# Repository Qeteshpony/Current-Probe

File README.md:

# Current-Probe

[Hardware Documentation](https://qeteshpony.github.io/Current-Probe)

A simple board to turn any oscilloscope into a current meter by running the load through the 4mm Terminals and connecting your oscilloscope to the BNC terminal. 

The resistor footprint takes a 2512 SMD resistor which usually come with a rating of 1 to 3, sometimes 5 watts which is enough to run several amps through this board. 

The connector footprints are made for the `Altech/Hirschmann PB 4` 4mm test jacks that take a standard 4mm test lead. 

The BNC connector footprint is for the `Amphenol B6252HB` but there's lots of cheap, compatible connectors with the same footprint available

You can also use the M3 screw holes to connect to this board since they are wired in parallel to the connectors closest to each.

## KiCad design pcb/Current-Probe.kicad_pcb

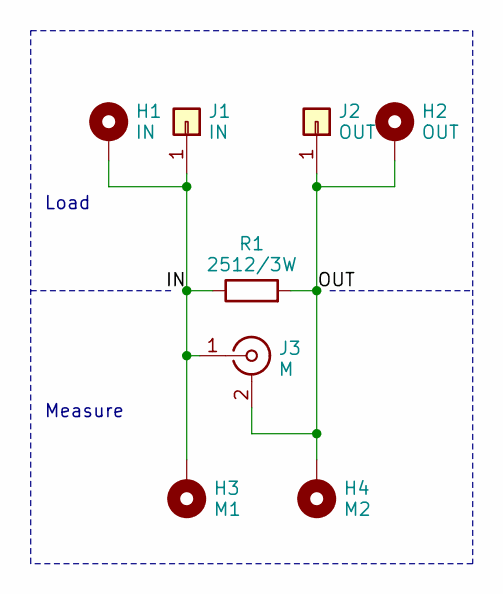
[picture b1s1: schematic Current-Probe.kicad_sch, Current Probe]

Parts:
H1: IN; MountingHole_3.2mm_M3_Pad_Via
H2: OUT; MountingHole_3.2mm_M3_Pad_Via
H3: M1; MountingHole_3.2mm_M3_Pad_Via
H4: M2; MountingHole_3.2mm_M3_Pad_Via
J1: IN; 4mm_print_socket_with_hole
J2: OUT; 4mm_print_socket_with_hole
J3: M; BNC_Amphenol_B6252HB-NPP3G-50_Horizontal
R1: 2512/3W; R_2512_6332Metric_Pad1.40x3.35mm_HandSolder

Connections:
/IN: H1.1, H3.1, J1.1, J3.1 (In), R1.1
/OUT: H2.1, H4.1, J2.1, J3.2 (Ext), R1.2

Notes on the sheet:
Measure
Load

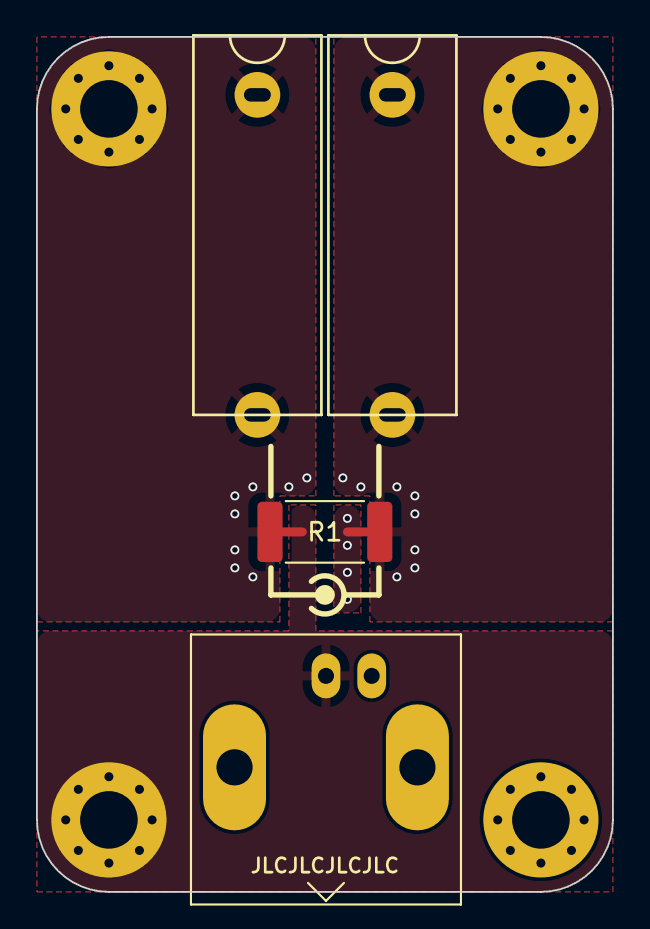
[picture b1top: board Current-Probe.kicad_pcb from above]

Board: 2 copper layers, 32.0 x 47.5 mm, 8 parts (0 on the bottom side), 2 nets.

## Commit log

2023-08-10 feat: initial commit
2023-08-10 chore(main): release 1.0.0
2023-08-10 docs: add more details
2023-08-10 style: renumber the connectors
    The different number order between the two connector sets triggered me...
2023-08-12 feat: add BNC connector
2023-08-12 feat: remove 4mm sockets on measuring side
    These were not needed anymore since the board will just be used with an oscilloscope anyway. The BNC connector does the job perfectly fine...
2023-08-12 chore(main): release 1.1.0
2023-08-12 docs: update readme
2024-08-29 ci: remove dependency between jobs
